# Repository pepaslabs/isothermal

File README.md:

# isothermal

An Arduino shield which regulates temperature.  Originally, this was used to regulate the temperature of a Hammond 1590BB.

- [schematic](kicad/releases/v1.2/isothermal.pdf)
- [gerber files](kicad/releases/v1.2)
- [OSHPark link](https://oshpark.com/shared_projects/9wWvXwMw)
- [EEVBlog discussion](http://www.eevblog.com/forum/metrology/temperature-stabilised-enclosures-heating-and-or-cooling/msg1407134/#msg1407134)

The resistor values were chosen to map a 20C to 30C window onto (roughly) 0V to 3.3V.

See also [this link](https://github.com/cellularmitosis/logs/tree/master/20180126-25c-chamber-tuning) for PID tuning and measurements of a similar design (based on MCP9701 rather than thermistors).

## Bill of Materials (BOM)

FIXME: update this BOM for v1.2.

- (1) LM324 op amp, DIP14.
  - [Tayda](https://www.taydaelectronics.com/lm324n-lm324-324-low-power-quad-op-amp-ic.html).
- (1) 2N3904 TO-92 NPN transistor.
  - Almost any TO-92 transistor should work here.
  - [Tayda](https://www.taydaelectronics.com/t-transistors/2n-series/2n3904-npn-general-propose-transistor.html).
  - The footprint is for a TO-220, in case you need to use a bigger transistor.
- (2) 10k thermistors.
  - I use Vishay [NTCLG100E2103JB](http://www.vishay.com/docs/29050/ntclg100.pdf) which are about $1 each from [Digi-key](https://www.digikey.com/product-detail/en/vishay-bc-components/NTCLG100E2103JB/BC2531-ND/773999).
  - You could also get away with [cheap epoxy bead thermistors](https://www.taydaelectronics.com/thermistors/10k-ohm-ntc-thermistor-5mm.html), though if the Beta is different you'll need to calibrate the gain of your controller.
- 1/4W resistors, 1% metal film (precision-ish):
  - (2) 10k.
  - (4) 33k.
  - (2) 120k.
  - [Tayda](https://www.taydaelectronics.com/resistors/1-4w-metal-film-resistors/test-group-2.html).
- 1/4W resistors (non-precision):
  - (1) 100R
  - (1) 470R
    - The LED resistor -- 330R or 220R will also work.
  - (1) 1k
  - (4) 100k
  - [Tayda](https://www.taydaelectronics.com/resistors/1-4w-metal-film-resistors/test-group-2.html).
- (9) 0.1uF ceramic capacitors, through-hole or 0805.
  - [Tayda](https://www.taydaelectronics.com/capacitors/ceramic-disc-capacitors/10-x-0-01uf-50v-ceramic-disc-capacitor-pkg-of-10.html).
- (1) 10uF electrolytic capacitor, 25V, 5mm diameter, 0.1" (2.5mm) lead spacing.
  - [Tayda](https://www.taydaelectronics.com/capacitors/electrolytic-capacitors/10uf-25v-105c-radial-electrolytic-capacitor-5x11mm.html).
- (1) 3mm LED.
  - [Tayda](https://www.taydaelectronics.com/led-3mm-green.html).
- (4) 2-pole terminal block, linkable, 0.2" lead spacing.
  - [Digi-key](https://www.digikey.com/product-detail/en/on-shore-technology-inc/OSTTA024163/ED2580-ND/614529).
  - Note: don't get the cheap (ebay) ones with the phillips-head screws -- the screws are garbage and the heads will strip.  If you go cheap, get the flat-head screws.  I ordered these and they seem to do the job: https://www.ebay.com/itm/182525842695
  - I'm not sure the [Tayda](https://www.taydaelectronics.com/connectors-sockets/terminal-blocks/pcb-mount/dg300-screw-terminal-block-2-positions-5mm.html) parts will work, as they are 5mm spacing, rather than 5.08mm, which might be a problem when you link 4 of them together and expect them to fit into 0.2" holes.
- 0.1" male headers: a block of 10, 8, 8, and 6.
  - These are the Arduino pins.
  - Actually, you only need 10 pins: 3.3V, 5V, GND, GND, A0, A1, AREF, AREF's GND, D3, D2.

If you are using this to heat a Hammon 1590BB, you'll also need:
- (1) Hammond 1590BB Aluminum enclosure.
  - [Tayda](https://www.taydaelectronics.com/hardware/enclosures/1590bb-style/1590bb-style-aluminum-diecast-enclosure.html).
- 1/2W or 1W (heater) resistors.
  - (10) 10R
    - [Tayda](https://www.taydaelectronics.com/resistors/1w-metal-film-resistors/resistor-10-ohm-1w-1-metal-film-pkg-of-10.html).
- Some thermal epoxy.  Arctic Silver is easy to source.  [Walmart](https://www.walmart.com/ip/Arctic-Silver-Alumina-Premium-Ceramic-Thermal-Adhesive/20449152) has it for $6 at the moment.
- (2) "craft foam" (9x12 sheets, 6mm)
  - [Amazon](https://www.amazon.com/Bulk-Buy-Foamies-10-Pack-1199-21/dp/B00KDMQB4Y).
- Hot glue to secure the foam to the Hammond case.
- Very thin gauge wire to connect the remote thermistor.  Scrap Ethernet twisted pairs will work (26 AWG), but 30 AWG "Kynar" (wire-wrap) wire is better (less error due to heat transfer along the wire).  Thin-gauge "magnet" wire will also work.
- An Arduino.

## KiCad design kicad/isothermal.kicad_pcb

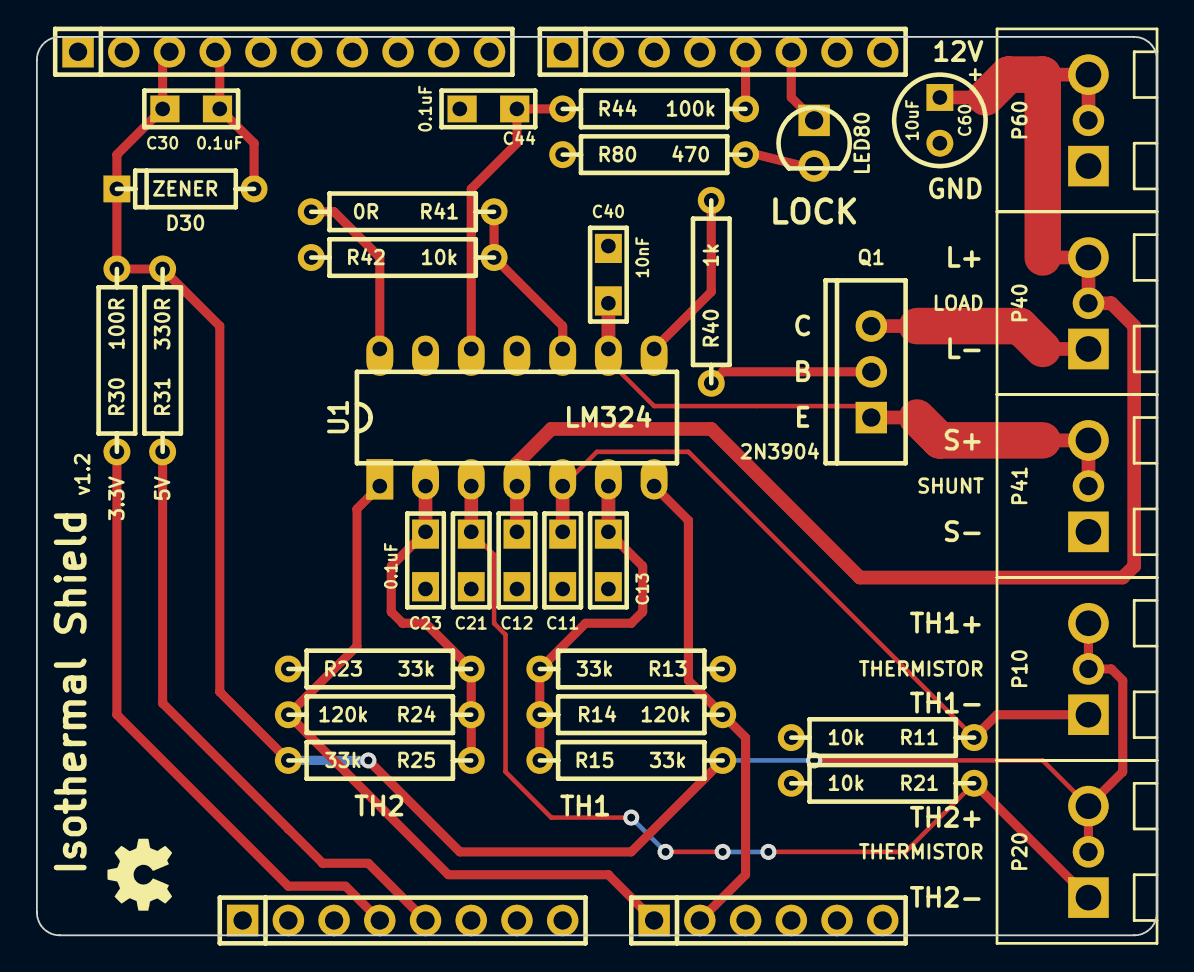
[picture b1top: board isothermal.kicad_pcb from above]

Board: 2 copper layers, 62.2 x 49.9 mm, 37 parts (0 on the bottom side), 22 nets.

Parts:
C11, C12, C13, C21, C23, C30, C44: 0.1uF; CERCAP_15_059B_0805
C40: 10nF; CERCAP_15_059B_0805
C60: 10uF; ELCAP_10_20_V_059A
D30: ZENER; DIODE_SS_059A_03_PL
LED80: LED; LED_3MM_069A
P10, P20, P40, P41, P60: CONN_2X1; TERMINAL_BLOCK_2_5mm
P70: CONN_6X1; SIL-6
P71, P73: CONN_8X1; SIL-8
P72: CONN_10X1; SIL-10
Q1: 2N3904; TO-220_V_069A
R11, R21, R42: 10k; R_AXIAL_0W25_059A_PL
R13, R15, R23, R25: 33k; R_AXIAL_0W25_059A_PL
R14, R24: 120k; R_AXIAL_0W25_059A_PL
R30: 100R; R_AXIAL_0W25_059A_PL
R31: 330R; R_AXIAL_0W25_059A_PL
R40: 1k; R_AXIAL_0W25_059A_PL
R41: 0R; R_AXIAL_0W25_059A_PL
R44: 100k; R_AXIAL_0W25_059A_PL
R80: 470; R_AXIAL_0W25_059A_PL
U1: LM324; DIP14_PL

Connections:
3V3: P71.4, R30.1
5V: P71.5, R31.1
12V: C12.1, C60.1, P40.2, P60.2, U1.4
A0: P70.1, R24.2, U1.1
A1: P70.2, R14.2, U1.7
AGND: C30.2, D30.1, P72.4
AREF: C30.1, D30.2, P10.2, P20.2, P72.3, R15.2, R25.2, R30.2, R31.2
D2: LED80.1, P73.6
D3: P73.5, R44.2
GND: C11.2, C12.2, C13.2, C21.2, C23.2, C40.2, C44.2, C60.2, P41.1, P60.1, P71.6, P71.7, R11.2, R13.1, R21.2, R23.1, R42.1, R80.1, U1.11
unnamed: R41.2, U1.13, U1.14
unnamed: R41.1, R42.2, U1.10
unnamed: R40.2, U1.8
unnamed: LED80.2, R80.2
unnamed: Q1.2, R40.1
unnamed: C44.1, R44.1, U1.12
unnamed: C11.1, P10.1, R11.1, U1.5
unnamed: C13.1, R13.2, R14.1, R15.1, U1.6
unnamed: C21.1, P20.1, R21.1, U1.3
unnamed: C23.1, R23.2, R24.1, R25.1, U1.2
unnamed: P40.1, Q1.3
unnamed: C40.1, P41.2, Q1.1, U1.9

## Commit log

2018-01-28 initial release
2018-01-28 board shots
2018-01-28 readme
2018-02-11 gitignore
2018-02-11 relaxing claims of performance
2018-03-31 increasing terminal block hole size, fixing pin spacing
2018-03-31 v1.1
2018-04-28 adding ptf56 resistor ltspice calculation
2018-06-08 adding additional resistor calculations
2018-06-08 more ltspice screenshots
2018-06-15 adding TODO
2018-06-22 v1.2
2018-07-05 svg foam insulation template
2018-07-05 svg as pdf
